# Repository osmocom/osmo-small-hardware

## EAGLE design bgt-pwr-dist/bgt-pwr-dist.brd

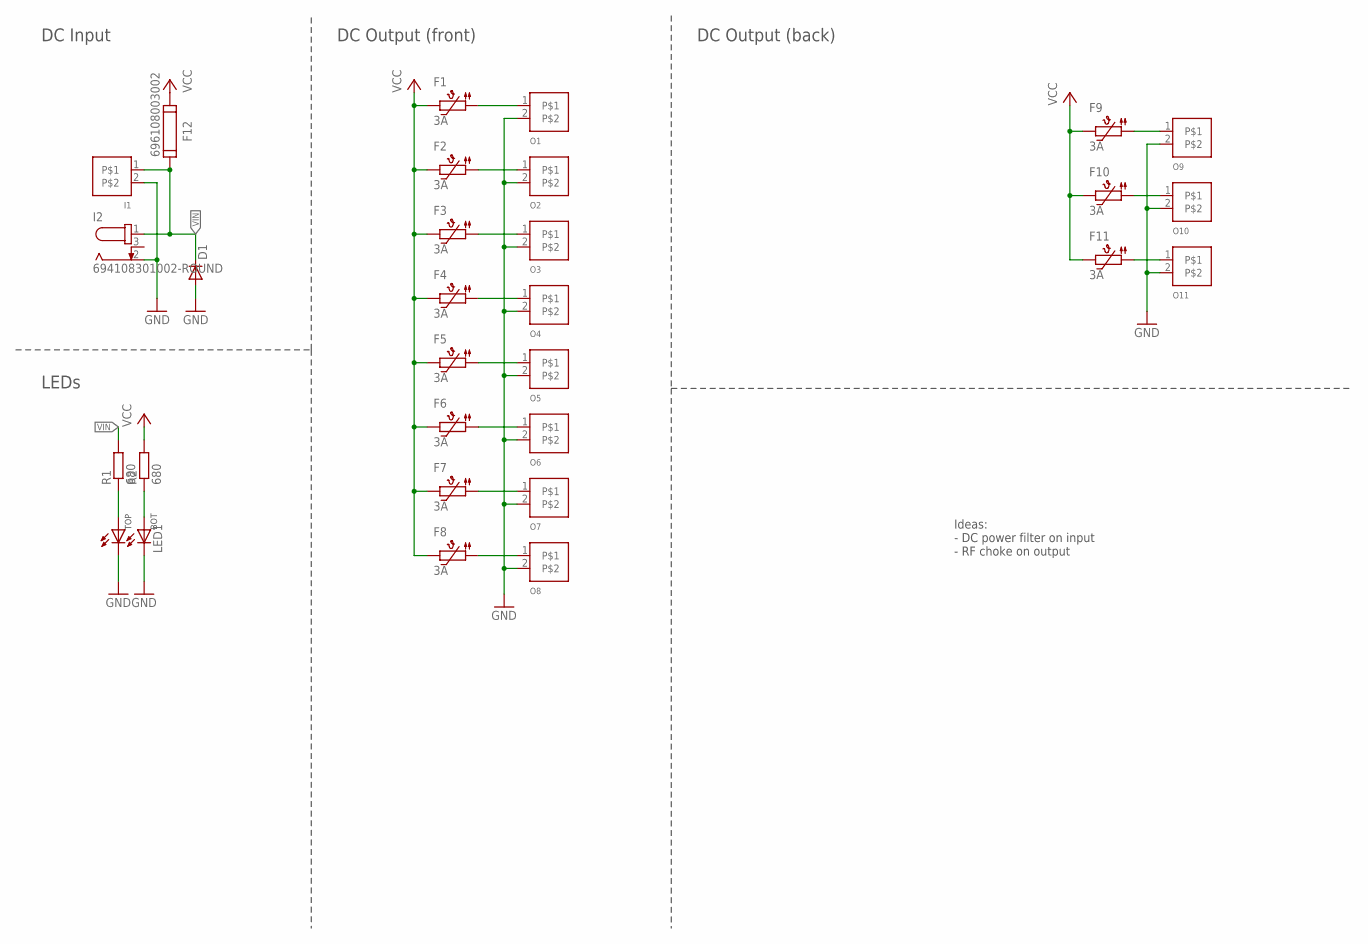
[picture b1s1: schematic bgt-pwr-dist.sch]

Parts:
D1: DIODE-DO201-15; DO201-15; MANUFACTURERPARTNUMBER 1N5351B
F1, F2, F3, F4, F5, F6, F7, F8, F9, F10, F11: 3A; 16R300G; MANUFACTURERPARTNUMBER 16R300GPR
F12: 696108003002; MANUFACTURERPARTNUMBER 696108003002
I1: RIA_1X2-230; RIA230; MANUFACTURERPARTNUMBER TBP01R1-508-02BE
I2: 694108301002-ROUND; 694108301002_ROUND; MANUFACTURERPARTNUMBER 694108301002
LED1: WP934MD; T-1; MANUFACTURERPARTNUMBER WP934MD/2GD
O1, O2, O3, O4, O5, O6, O7, O8, O9, O10, O11: RIA_1X2-382; RIA382-02; MANUFACTURERPARTNUMBER TBP02R1-381-02BE
R1, R2: 680; 0207/10; MANUFACTURERPARTNUMBER CF14JT680R

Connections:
GND: D1.A, I1.2, I2.2, LED1.1 (CT), LED1.3 (CB), O1.2, O2.2, O3.2, O4.2, O5.2, O6.2, O7.2, O8.2, O9.2, O10.2, O11.2
unnamed: F1.1, O1.1
unnamed: F3.1, O3.1
unnamed: F4.1, O4.1
unnamed: F5.1, O5.1
unnamed: F6.1, O6.1
unnamed: F7.1, O7.1
unnamed: F8.1, O8.1
unnamed: LED1.2 (AT), R1.1
unnamed: F9.1, O9.1
unnamed: F10.1, O10.1
unnamed: F11.1, O11.1
unnamed: LED1.4 (AB), R2.1
O2: F2.1, O2.1
VCC: F1.2, F2.2, F3.2, F4.2, F5.2, F6.2, F7.2, F8.2, F9.2, F10.2, F11.2, F12.2, R2.2
VIN: D1.C, F12.1, I1.1, I2.1, R1.2

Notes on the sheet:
Ideas: - DC power filter on input - RF choke on output
DC Input
LEDs
DC Output (front)
DC Output (back)

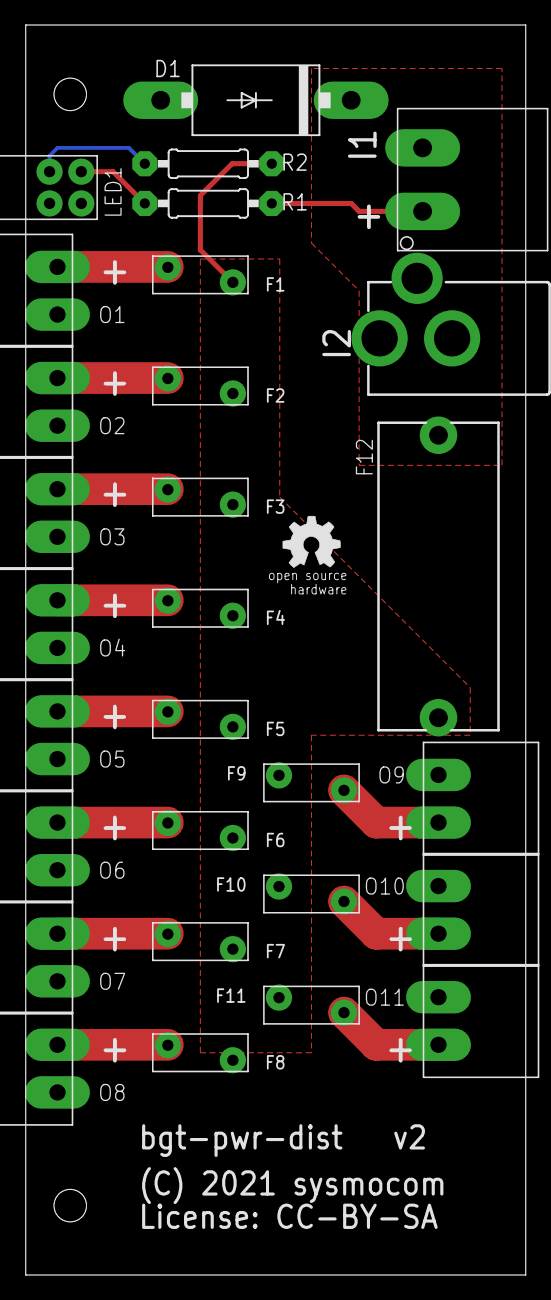
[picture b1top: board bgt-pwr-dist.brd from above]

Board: 2 copper layers, 40.0 x 100.0 mm, 32 parts (1 on the bottom side), 16 nets.

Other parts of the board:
U$1: BGT_3U_160
U$2, U$3: OSHW_5MM

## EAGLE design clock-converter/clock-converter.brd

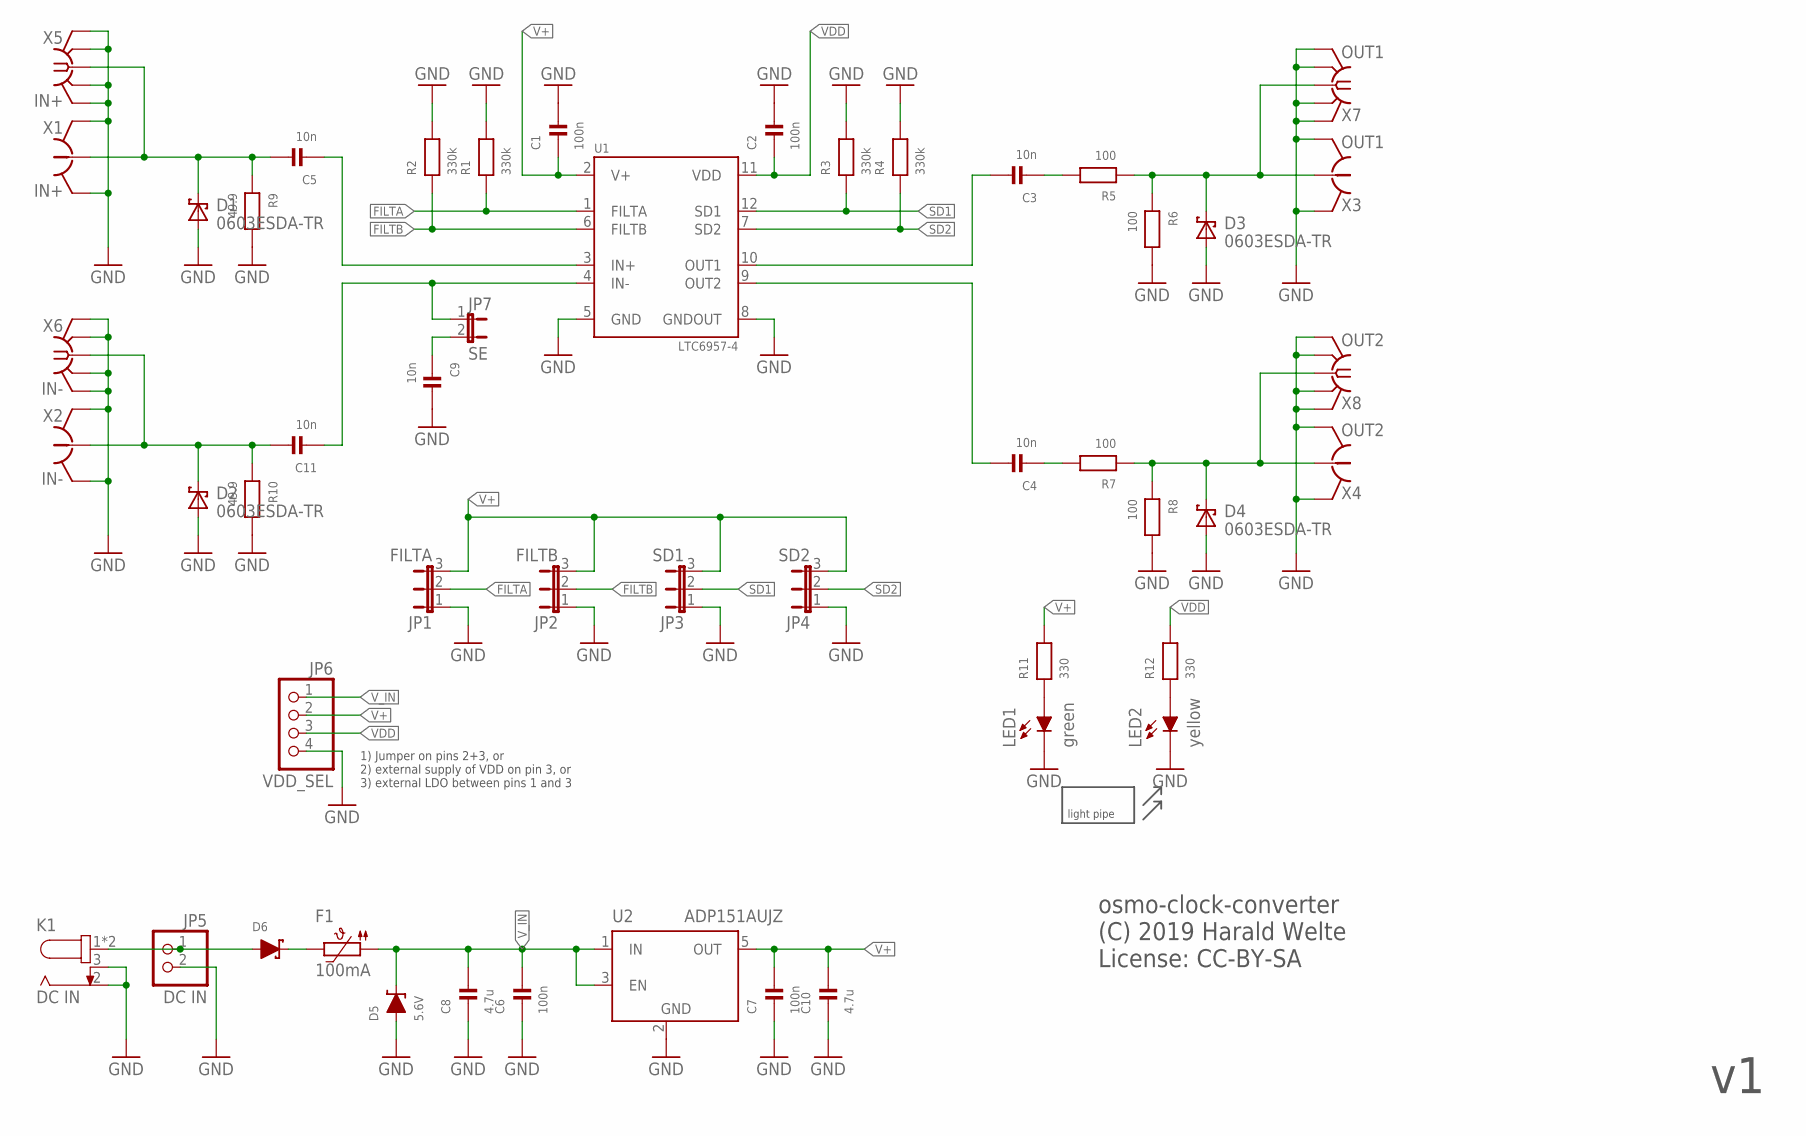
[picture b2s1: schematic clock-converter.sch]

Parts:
C1, C2, C6, C7: 100n; _0603; MANUFACTURERPARTNUMBER CL10B104KO8NNNC
C3, C4, C5, C9, C11: 10n; _0603; MANUFACTURERPARTNUMBER C0603C103M5RACTU
C8, C10: 4.7u; _0805; MANUFACTURERPARTNUMBER CL21A475KOFNNNE
D1, D2, D3, D4: 0603ESDA-TR; 0603; MANUFACTURERPARTNUMBER 0603ESDA2-TR2
D5: 5.6V; SMADIODE; MANUFACTURERPARTNUMBER 3SMAJ5919B-TP
D6: DIODE-SCHOTTKY-SMA; SMADIODE; MANUFACTURERPARTNUMBER CUS08F30,H3F
F1: 100mA; 1206L; MANUFACTURERPARTNUMBER 0ZCJ0020FF2E
JP1: FILTA; JP2; MANUFACTURERPARTNUMBER 61300311121
JP2: FILTB; JP2; MANUFACTURERPARTNUMBER 61300311121
JP3: SD1; JP2; MANUFACTURERPARTNUMBER 61300311121
JP4: SD2; JP2; MANUFACTURERPARTNUMBER 61300311121
JP5: DC IN; 1X02; MANUFACTURERPARTNUMBER PREC002SAAN-RC
JP6: VDD_SEL; 1X04; MANUFACTURERPARTNUMBER PRPC004SAAN-RC
JP7: SE; JP1; MANUFACTURERPARTNUMBER PREC002SAAN-RC
K1: DC IN; 694108106102; MANUFACTURERPARTNUMBER 694108106102
LED1: green; PLCC2-MIN; MANUFACTURERPARTNUMBER LG T67F-R1T1-24
LED2: yellow; PLCC2-MIN; MANUFACTURERPARTNUMBER LY T676-S1T1-26-Z
M1: MENTOR_12701001; 1270.1001; MANUFACTURERPARTNUMBER UNKNOWN MANUFACTURER PART NUMBER
R1, R2, R3, R4: 330k; _0603; MANUFACTURERPARTNUMBER RMCF0603JG330K
R5, R6, R7, R8: 100; _0603; MANUFACTURERPARTNUMBER RMCF0603JT100R
R9, R10: 49.9; _0603; MANUFACTURERPARTNUMBER RMCF0603FT49R9
R11, R12: 330; _0603; MANUFACTURERPARTNUMBER RMCF0603JT330R
U1: LTC6957-4; MSOP12; MANUFACTURERPARTNUMBER LTC6957IMS-3#PBF
U2: ADP151AUJZ; SOT23L; MANUFACTURERPARTNUMBER ADP151AUJZ-3.0-R7
X1: IN+; HRS_UFL; MANUFACTURERPARTNUMBER U.FL-R-SMT(10)
X2: IN-; HRS_UFL; MANUFACTURERPARTNUMBER U.FL-R-SMT(10)
X3: OUT1; HRS_UFL; MANUFACTURERPARTNUMBER U.FL-R-SMT(10)
X4: OUT2; HRS_UFL; MANUFACTURERPARTNUMBER U.FL-R-SMT(10)
X5: IN+; SMA-F-S-TH; MANUFACTURERPARTNUMBER 619540-1
X6: IN-; SMA-F-S-TH; MANUFACTURERPARTNUMBER 619540-1
X7: OUT1; SMA-F-S-TH; MANUFACTURERPARTNUMBER 619540-1
X8: OUT2; SMA-F-S-TH; MANUFACTURERPARTNUMBER 619540-1

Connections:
FILTA: JP1.2, R1.1, U1.1 (FILTA)
FILTB: JP2.2, R2.1, U1.6 (FILTB)
GND: C1.2, C2.2, C6.1, C7.1, C8.1, C9.2, C10.1, D1.1 (A), D2.1 (A), D3.1 (A), D4.1 (A), D5.A, JP1.1, JP2.1, JP3.1, JP4.1, JP5.2, JP6.4, K1.2, K1.3, LED1.K (C), LED2.K (C), R1.2, R2.2, R3.2, R4.2, R6.2, R8.2, R9.2, R10.2, U1.5 (GND), U1.8 (GNDOUT), U2.2 (GND), X1.GND@1 (GND), X1.GND@2 (GND), X2.GND@1 (GND), X2.GND@2 (GND), X3.GND@1 (GND), X3.GND@2 (GND), X4.GND@1 (GND), X4.GND@2 (GND), X5.G1 (GND), X5.G2 (GND), X5.G3 (GND), X5.G4 (GND), X6.G1 (GND), X6.G2 (GND), X6.G3 (GND), X6.G4 (GND), X7.G1 (GND), X7.G2 (GND), X7.G3 (GND), X7.G4 (GND), X8.G1 (GND), X8.G2 (GND), X8.G3 (GND), X8.G4 (GND)
IN+: C5.1, U1.3 (IN+)
unnamed: LED1.A, R11.1
unnamed: C3.2, U1.10 (OUT1)
unnamed: LED2.A, R12.1
unnamed: C9.1, JP7.2
unnamed: D6.C, F1.2
unnamed: C3.1, R5.2
unnamed: C11.1, JP7.1, U1.4 (IN-)
unnamed: C4.2, U1.9 (OUT2)
unnamed: C4.1, R7.2
unnamed: C11.2, D2.2 (K), R10.1, X2.SIG (1), X6.C (1)
unnamed: C5.2, D1.2 (K), R9.1, X1.SIG (1), X5.C (1)
unnamed: D6.A, JP5.1, K1.1, K1.1-1 (1)
OUT1: D3.2 (K), R5.1, R6.1, X3.SIG (1), X7.C (1)
OUT2: D4.2 (K), R7.1, R8.1, X4.SIG (1), X8.C (1)
SD1: JP3.2, R3.1, U1.12 (SD1)
SD2: JP4.2, R4.1, U1.7 (SD2)
V+: C1.1, C7.2, C10.2, JP1.3, JP2.3, JP3.3, JP4.3, JP6.2, R11.2, U1.2 (V+), U2.5 (OUT)
VDD: C2.1, JP6.3, R12.2, U1.11 (VDD)
V_IN: C6.2, C8.2, D5.C, F1.1, JP6.1, U2.1 (IN), U2.3 (EN)

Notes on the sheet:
1) Jumper on pins 2+3, or 2) external supply of VDD on pin 3, or 3) external LDO between pins 1 and 3
osmo-clock-converter (C) 2019 Harald Welte License: CC-BY-SA

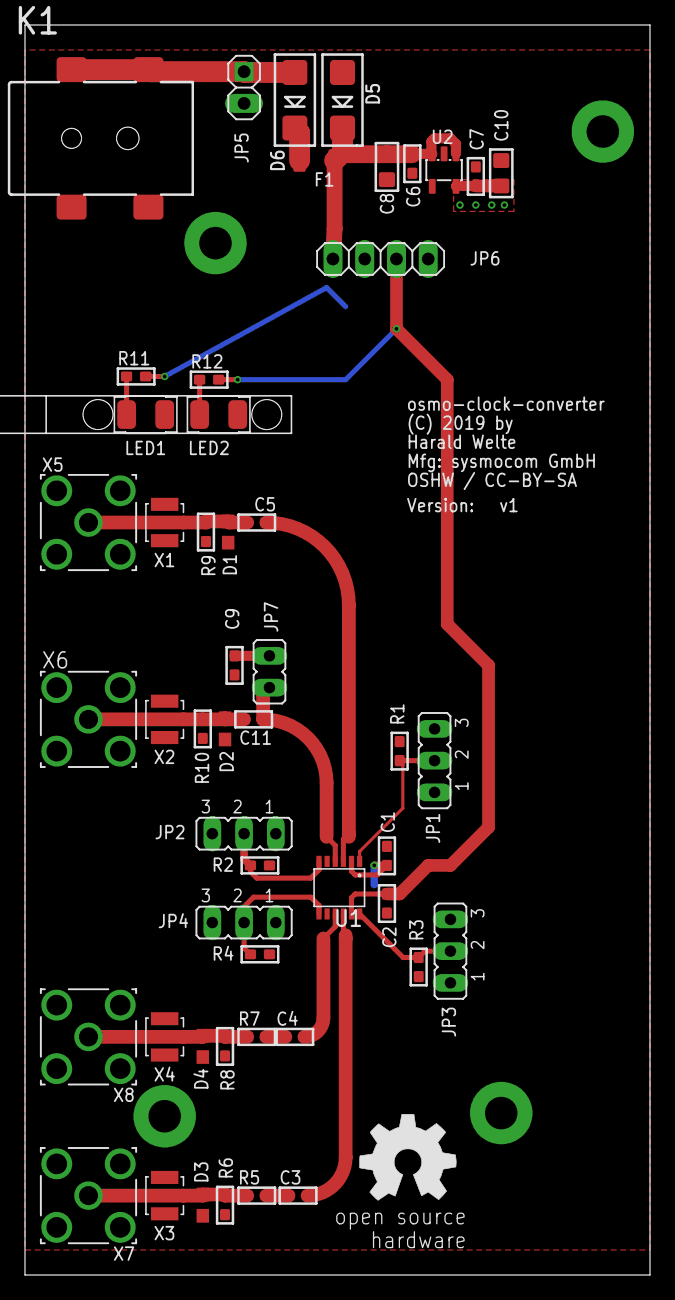
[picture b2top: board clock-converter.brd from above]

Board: 2 copper layers, 50.0 x 100.0 mm, 52 parts (0 on the bottom side), 23 nets.

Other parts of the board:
U$1: OSHW_8MM

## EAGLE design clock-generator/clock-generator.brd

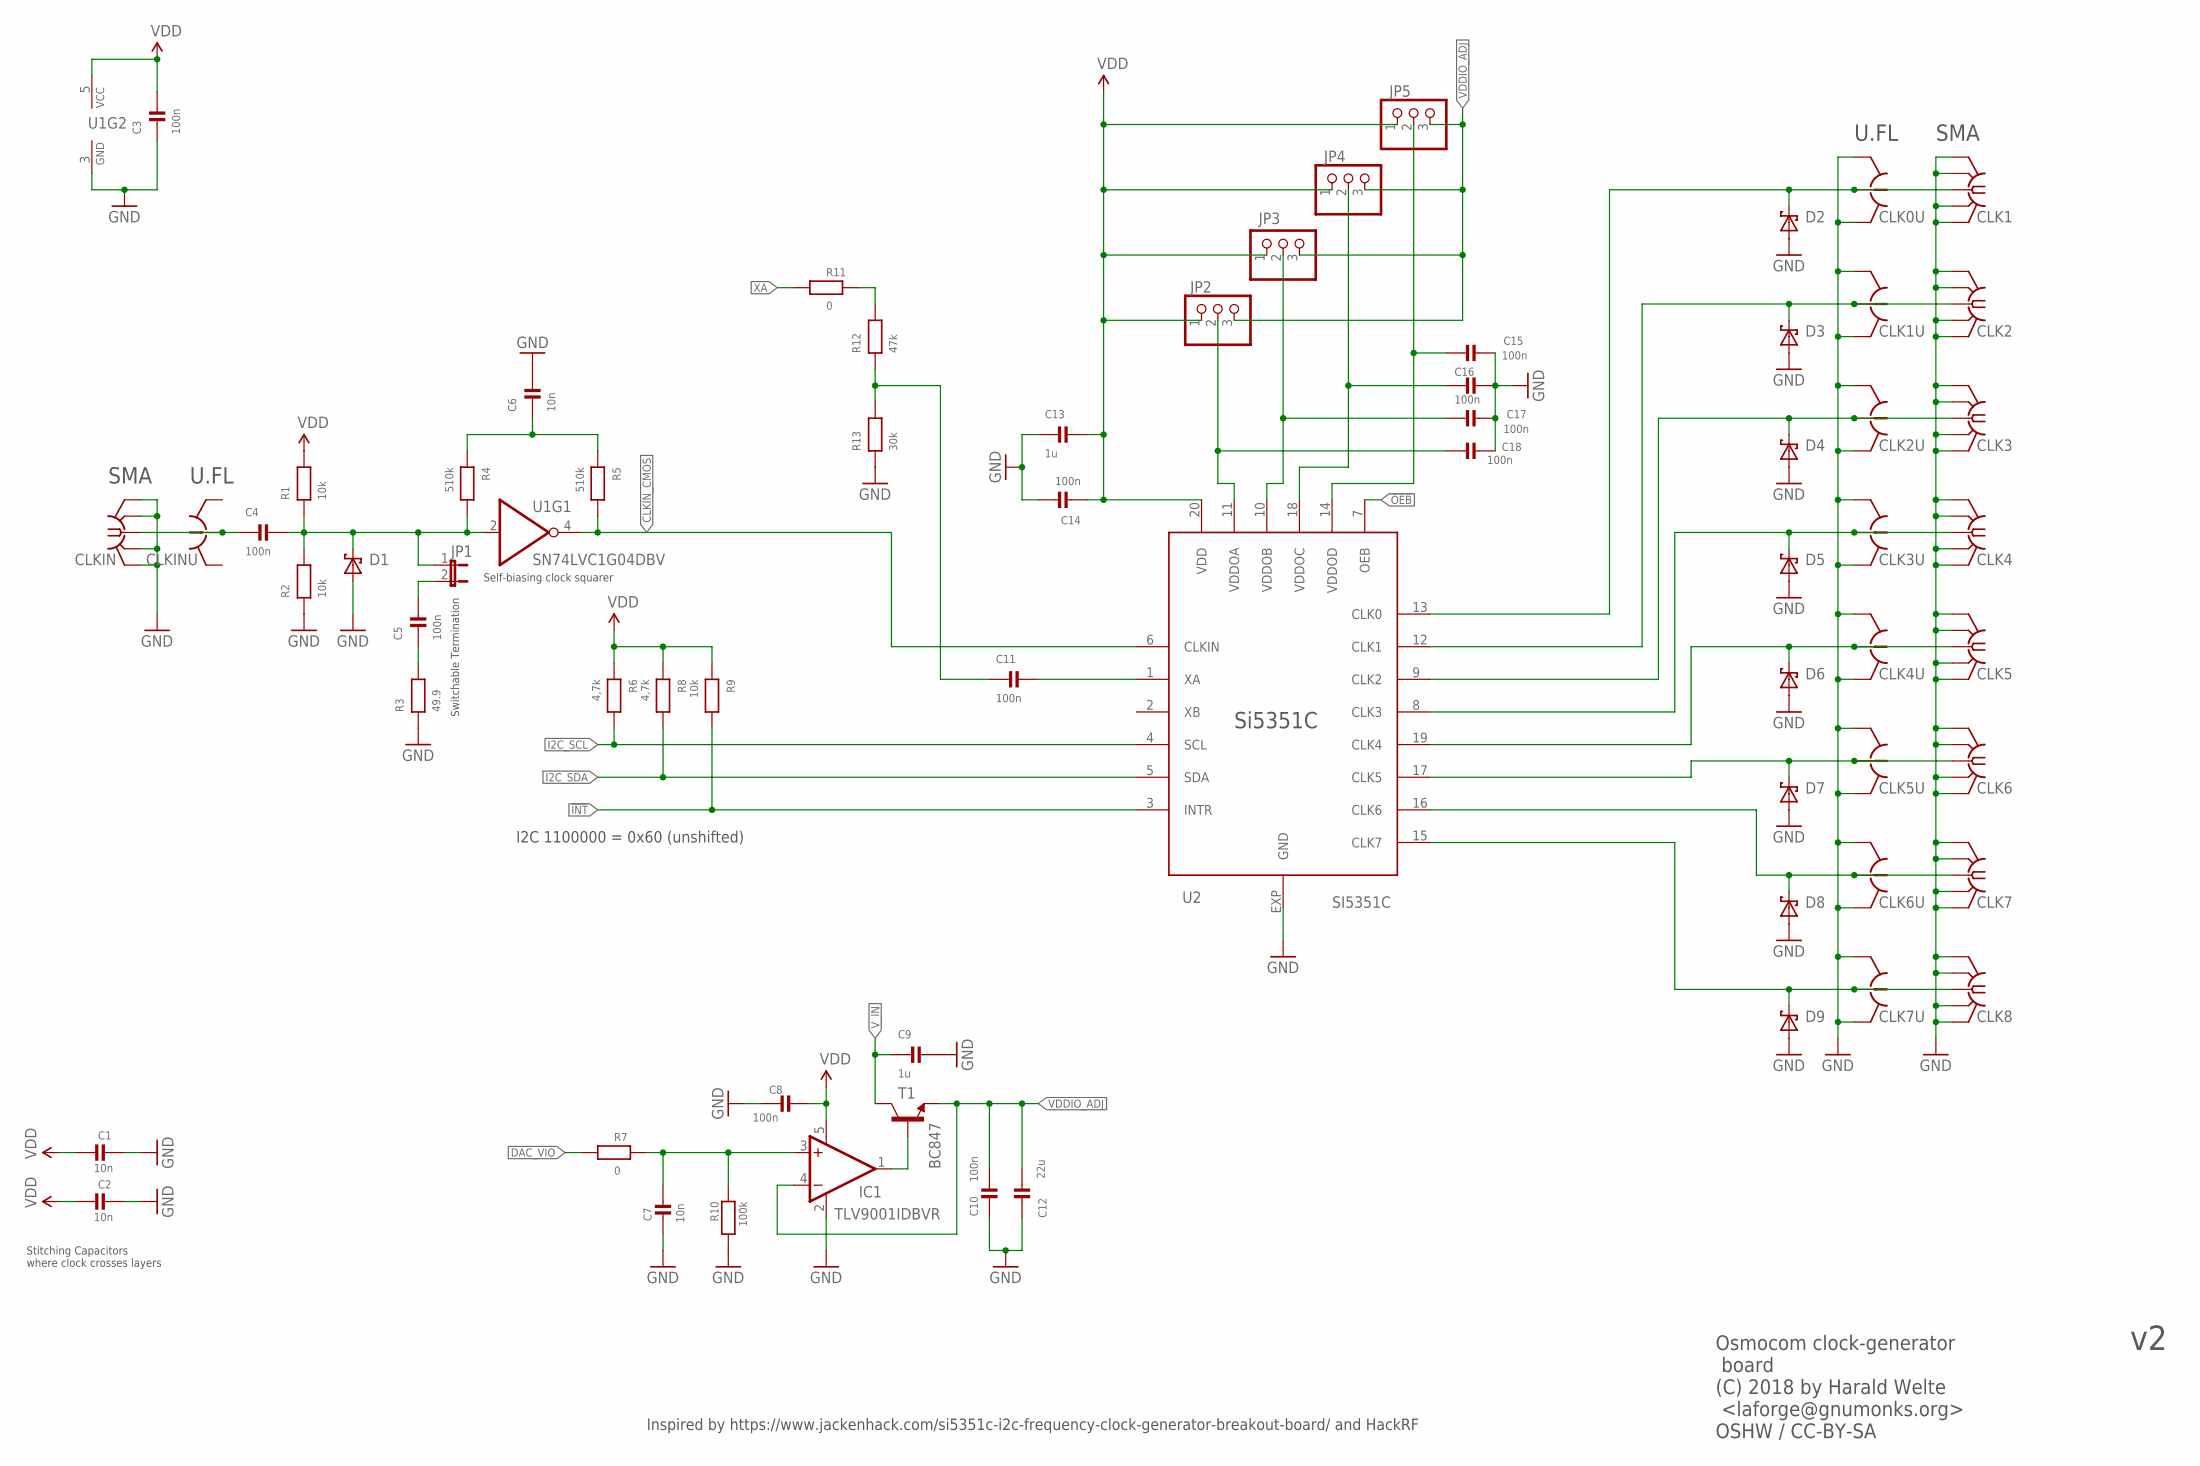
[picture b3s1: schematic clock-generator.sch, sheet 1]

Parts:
C1, C2, C6, C7: 10n; _0402; MANUFACTURERPARTNUMBER CL05B103KA5NNNC
C3, C4, C5, C11, C14: 100n; _0603; MANUFACTURERPARTNUMBER CL10B104KO8NNNC
C8, C10, C15, C16, C17, C18: 100n; _0402; MANUFACTURERPARTNUMBER GCM155R71C104KA55J
C9, C13: 1u; _0603; MANUFACTURERPARTNUMBER CL10A105KP8NNNC
C12: 22u; _0805; MANUFACTURERPARTNUMBER CL21A226MQQNNNE
CLK0U, CLK1U, CLK2U, CLK3U, CLK4U, CLK5U, CLK6U, CLK7U: HRS_UFL; MANUFACTURERPARTNUMBER U.FL-R-SMT(10)
CLK1, CLK2, CLK3, CLK4, CLK5, CLK6, CLK7, CLK8: SMA-F-S-TH; MANUFACTURERPARTNUMBER 619540-1
CLKIN: SMA-F-S-TH; MANUFACTURERPARTNUMBER 619540-1
CLKINU: HRS_UFL; MANUFACTURERPARTNUMBER U.FL-R-SMT(10)
D1, D2, D3, D4, D5, D6, D7, D8, D9: 0603ESDA-TR; 0603; MANUFACTURERPARTNUMBER 0603ESDA2-TR2
IC1: TLV9001IDBVR; SOT23-5; MANUFACTURERPARTNUMBER TLV9001IDBVR
JP1: JP1E; JP1; MANUFACTURERPARTNUMBER PREC002SAAN-RC
JP2, JP3, JP4, JP5: PINHD-1X03_2.54-S; 1X03-S; MANUFACTURERPARTNUMBER UNKNOWN MANUFACTURER PART NUMBER
R1, R2, R9: 10k; _0603; MANUFACTURERPARTNUMBER RMCF0603JT10K0
R3: 49.9; _0603; MANUFACTURERPARTNUMBER RMCF0603FT49R9
R4, R5: 510k; _0603; MANUFACTURERPARTNUMBER RC0603FR-07510KL
R6, R8: 4,7k; _0603; MANUFACTURERPARTNUMBER RC0603JR-074K7L
R7, R11: 0; _0603; MANUFACTURERPARTNUMBER RC1608J000CS
R10: 100k; _0603; MANUFACTURERPARTNUMBER RC0603JR-07100KL
R12: 47k; _0603; MANUFACTURERPARTNUMBER RC0603JR-0747KL
R13: 30k; _0603; MANUFACTURERPARTNUMBER RC0603JR-0730KL
T1: BC847; SOT23-BEC; MANUFACTURERPARTNUMBER BC847C,215
U1: SN74LVC1G04DBV; DBV0005A; MANUFACTURERPARTNUMBER SN74LVC1G04DBVR
U2: SI5351C; QFN-20; MANUFACTURERPARTNUMBER SI5351C-B-GMR

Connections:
!INT: R9.2, U2.3 (INTR); also elsewhere on the board
!OEB: U2.7 (OEB); also elsewhere on the board
CLK0_LINE: CLK0U.SIG (1), CLK1.C (1), D2.2 (K), U2.13 (CLK0)
CLK1_LINE: CLK1U.SIG (1), CLK2.C (1), D3.2 (K), U2.12 (CLK1)
CLK2_LINE: CLK2U.SIG (1), CLK3.C (1), D4.2 (K), U2.9 (CLK2)
CLK3_LINE: CLK3U.SIG (1), CLK4.C (1), D5.2 (K), U2.8 (CLK3)
CLK4_LINE: CLK4U.SIG (1), CLK5.C (1), D6.2 (K), U2.19 (CLK4)
CLK5_LINE: CLK5U.SIG (1), CLK6.C (1), D7.2 (K), U2.17 (CLK5)
CLK6_LINE: CLK6U.SIG (1), CLK7.C (1), D8.2 (K), U2.16 (CLK6)
CLK7_LINE: CLK7U.SIG (1), CLK8.C (1), D9.2 (K), U2.15 (CLK7)
CLKIN: C4.1, CLKIN.C (1), CLKINU.SIG (1)
CLKIN_AC: C4.2, D1.2 (K), JP1.1, R1.1, R2.2, R4.2, U1.2 (I)
CLKIN_CMOS: R5.2, U1.4 (O), U2.6 (CLKIN)
DAC_VIO: R7.2; also elsewhere on the board
GND: C1.1, C2.1, C3.1, C6.2, C7.1, C8.1, C9.2, C10.1, C12.1, C13.1, C14.2, C15.2, C16.2, C17.2, C18.2, CLK0U.GND@1 (GND), CLK0U.GND@2 (GND), CLK1.G1 (GND), CLK1.G2 (GND), CLK1.G3 (GND), CLK1.G4 (GND), CLK1U.GND@1 (GND), CLK1U.GND@2 (GND), CLK2.G1 (GND), CLK2.G2 (GND), CLK2.G3 (GND), CLK2.G4 (GND), CLK2U.GND@1 (GND), CLK2U.GND@2 (GND), CLK3.G1 (GND), CLK3.G2 (GND), CLK3.G3 (GND), CLK3.G4 (GND), CLK3U.GND@1 (GND), CLK3U.GND@2 (GND), CLK4.G1 (GND), CLK4.G2 (GND), CLK4.G3 (GND), CLK4.G4 (GND), CLK4U.GND@1 (GND), CLK4U.GND@2 (GND), CLK5.G1 (GND), CLK5.G2 (GND), CLK5.G3 (GND), CLK5.G4 (GND), CLK5U.GND@1 (GND), CLK5U.GND@2 (GND), CLK6.G1 (GND), CLK6.G2 (GND), CLK6.G3 (GND), CLK6.G4 (GND), CLK6U.GND@1 (GND), CLK6U.GND@2 (GND), CLK7.G1 (GND), CLK7.G2 (GND), CLK7.G3 (GND), CLK7.G4 (GND), CLK7U.GND@1 (GND), CLK7U.GND@2 (GND), CLK8.G1 (GND), CLK8.G2 (GND), CLK8.G3 (GND), CLK8.G4 (GND), CLKIN.G1 (GND), CLKIN.G2 (GND), CLKIN.G3 (GND), CLKIN.G4 (GND), CLKINU.GND@1 (GND), CLKINU.GND@2 (GND), D1.1 (A), D2.1 (A), D3.1 (A), D4.1 (A), D5.1 (A), D6.1 (A), D7.1 (A), D8.1 (A), D9.1 (A), IC1.2 (V-), R2.1, R3.1, R10.1, R13.2, U1.3 (GND), U2.EXP (GND); also elsewhere on the board
I2C_SCL: R6.2, U2.4 (SCL); also elsewhere on the board
I2C_SDA: R8.2, U2.5 (SDA); also elsewhere on the board
unnamed: R11.1, R12.1
unnamed: C5.1, R3.2
unnamed: C11.1, R12.2, R13.1
unnamed: C6.1, R4.1, R5.1
unnamed: C5.2, JP1.2
unnamed: C11.2, U2.1 (XA)
unnamed: C7.2, IC1.3 (+IN), R7.1, R10.2
unnamed: IC1.1 (OUT), T1.B
VDD: C1.2, C2.2, C3.2, C8.2, C13.2, C14.1, IC1.5 (V+), JP2.1, JP3.1, JP4.1, JP5.1, R1.2, R6.1, R8.1, R9.1, U1.5 (VCC), U2.20 (VDD); also elsewhere on the board
VDDIO_ADJ: C10.2, C12.2, IC1.4 (-IN), JP2.3, JP3.3, JP4.3, JP5.3, T1.E
VDDOA: C18.1, JP2.2, U2.11 (VDDOA)
VDDOB: C17.1, JP3.2, U2.10 (VDDOB)
VDDOC: C16.1, JP4.2, U2.18 (VDDOC)
VDDOD: C15.1, JP5.2, U2.14 (VDDOD)
V_IN: C9.1, T1.C; also elsewhere on the board
XA: R11.2; also elsewhere on the board

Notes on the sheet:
Switchable Termination
Self-biasing clock squarer
I2C 1100000 = 0x60 (unshifted)
Stitching Capacitors where clock crosses layers
SMA
U.FL
Si5351C
Osmocom clock-generator board (C) 2018 by Harald Welte <laforge@gnumonks.org> OSHW / CC-BY-SA
Inspired by https://www.jackenhack.com/si5351c-i2c-frequency-clock-generator-breakout-board/ and HackRF

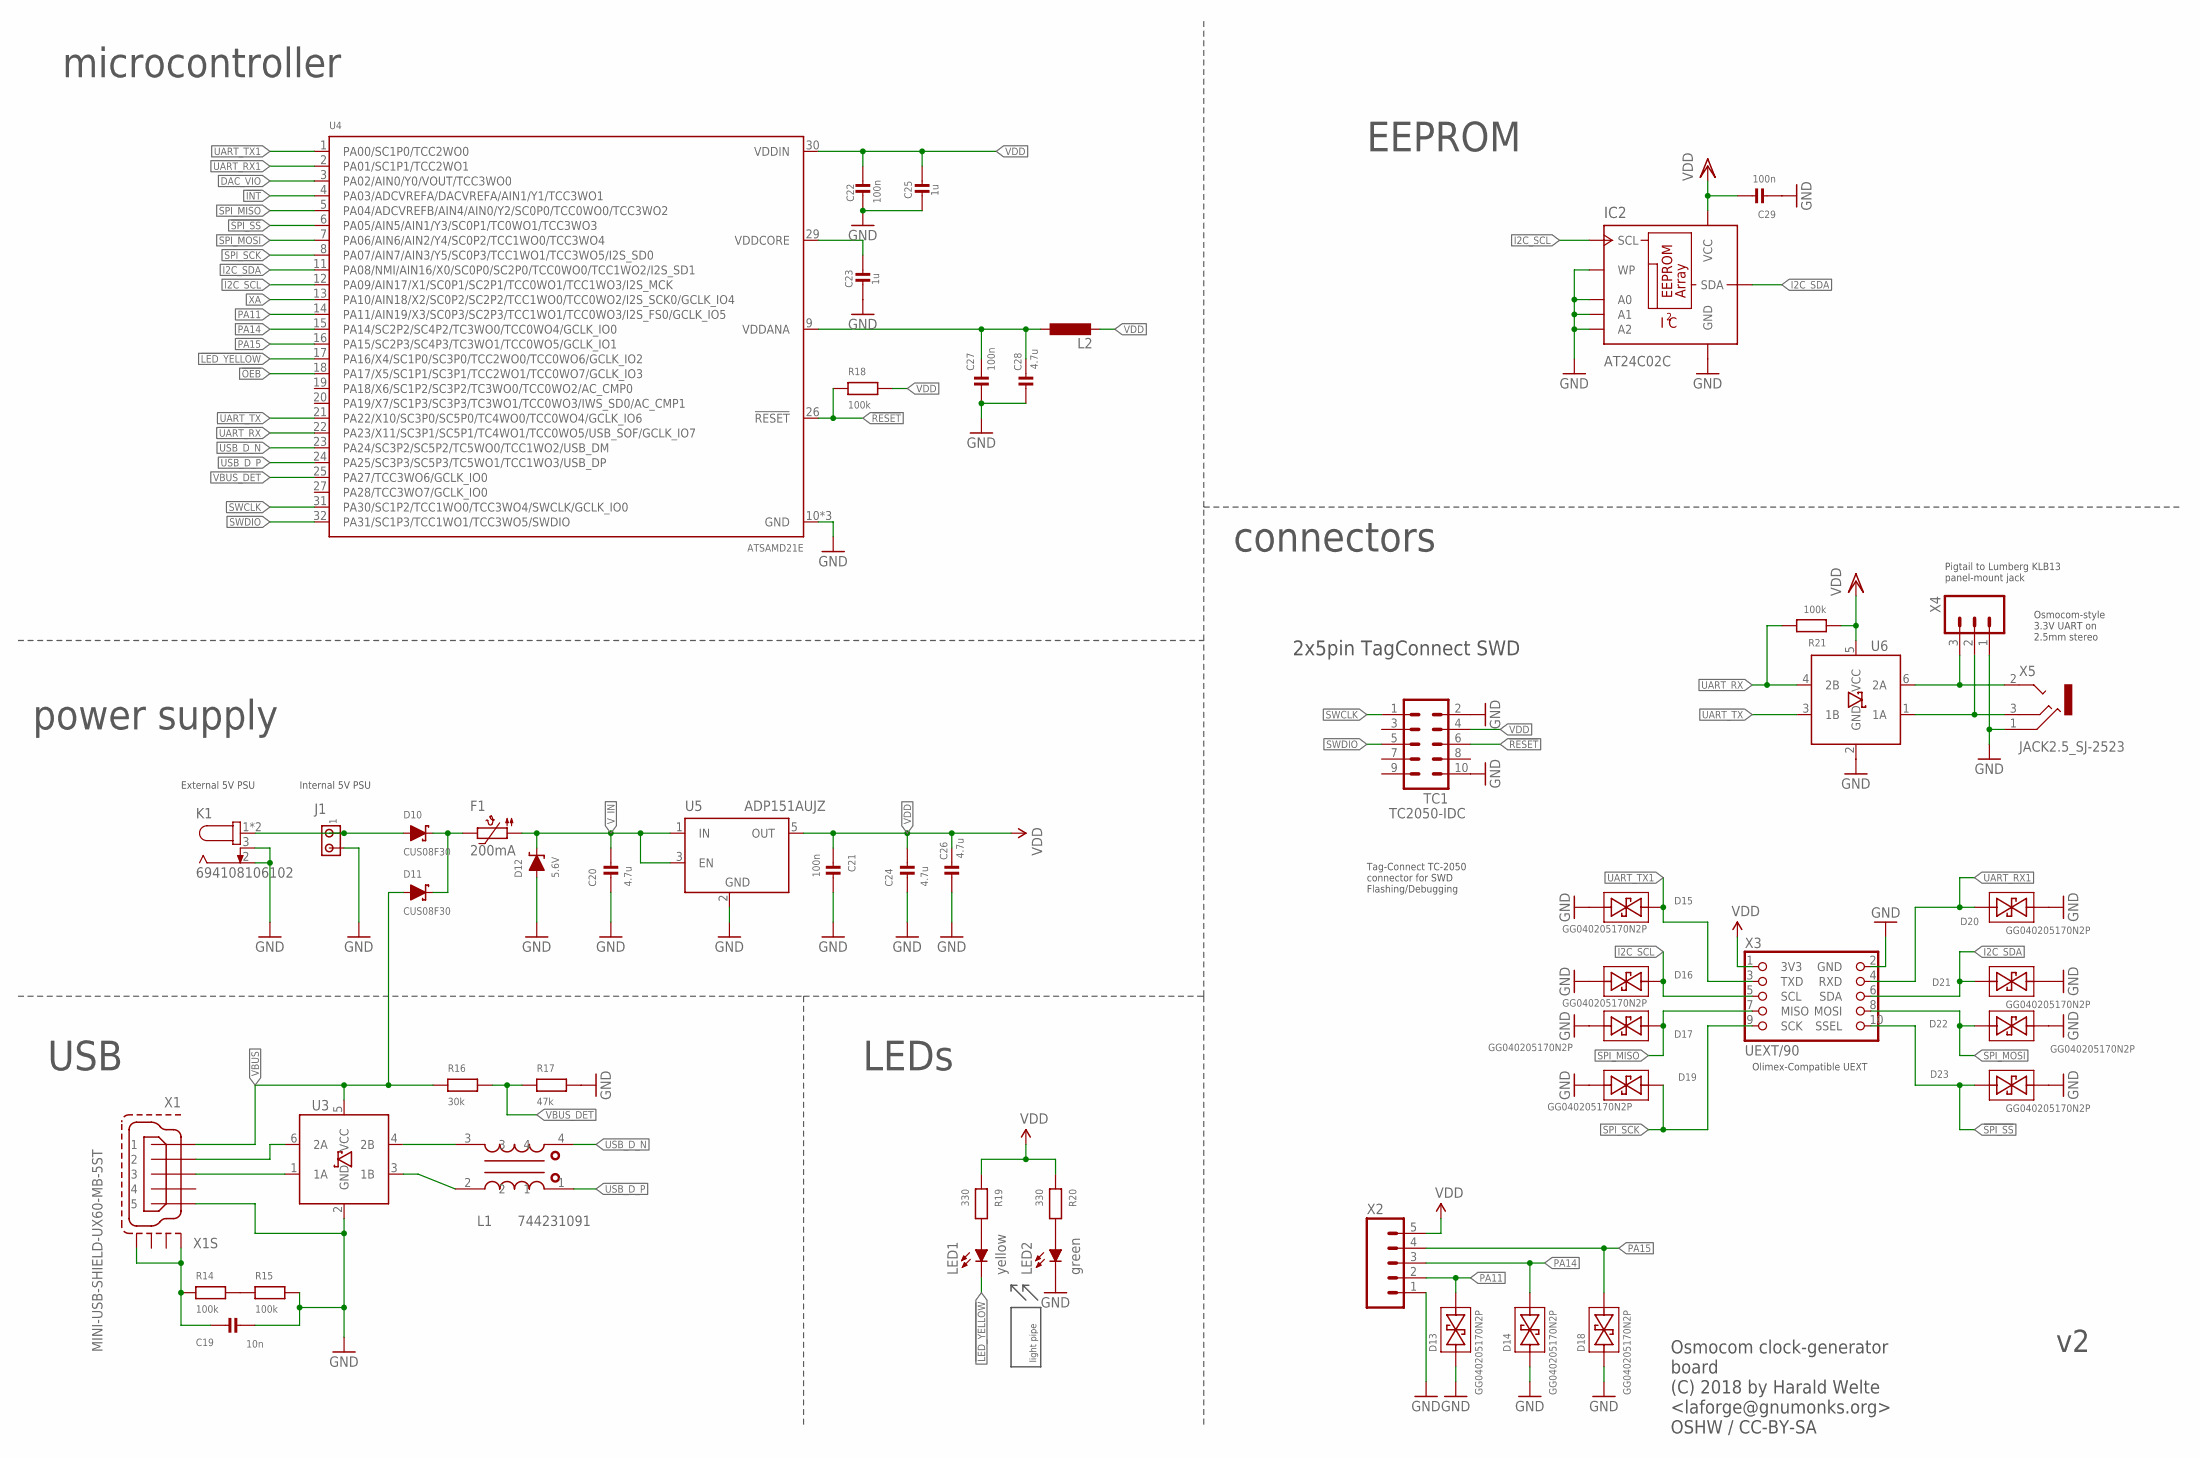
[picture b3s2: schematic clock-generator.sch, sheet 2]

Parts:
C19: 10n; _0402; MANUFACTURERPARTNUMBER CL05B103KA5NNNC
C20, C24, C26, C28: 4.7u; _0805; MANUFACTURERPARTNUMBER CL21A475KOFNNNE
C21, C29: 100n; _0603; MANUFACTURERPARTNUMBER CL10B104KO8NNNC
C22, C27: 100n; _0402; MANUFACTURERPARTNUMBER GCM155R71C104KA55J
C23, C25: 1u; _0603; MANUFACTURERPARTNUMBER CL10A105KP8NNNC
D10, D11: CUS08F30; SOD-323; MANUFACTURERPARTNUMBER CUS08F30,H3F
D12: 5.6V; SMADIODE; MANUFACTURERPARTNUMBER 3SMAJ5919B-TP
D13, D14, D15, D16, D17, D18, D19, D20, D21, D22, D23: GG040205170N2P; _0402; MANUFACTURERPARTNUMBER GG040205170N2P
F1: 200mA; 1206L; MANUFACTURERPARTNUMBER 0ZCJ0020FF2E
IC2: AT24C02C; TSSOP8; MANUFACTURERPARTNUMBER AT24C02C-XHM-T
J1: MTA02-100; 10X02MTA; MANUFACTURERPARTNUMBER UNKNOWN MANUFACTURER PART NUMBER
K1: 694108106102; MANUFACTURERPARTNUMBER 694108106102
L1: 744231091; WE-CNSW_0805; MANUFACTURERPARTNUMBER 744231091
L2: INDUCTOR_0805; _0805; MANUFACTURERPARTNUMBER 742792096
LED1: yellow; PLCC2-MIN; MANUFACTURERPARTNUMBER LY T676-S1T1-26-Z
LED2: green; PLCC2-MIN; MANUFACTURERPARTNUMBER LG T67F-R1T1-24
M1: MENTOR_12701001; 1270.1001; MANUFACTURERPARTNUMBER UNKNOWN MANUFACTURER PART NUMBER
R14, R15, R18, R21: 100k; _0603; MANUFACTURERPARTNUMBER RC0603JR-07100KL
R16: 30k; _0603; MANUFACTURERPARTNUMBER RC0603JR-0730KL
R17: 47k; _0603; MANUFACTURERPARTNUMBER RC0603JR-0747KL
R19, R20: 330; _0603; MANUFACTURERPARTNUMBER RMCF0603JT330R
TC1: TC2050-IDC; MANUFACTURERPARTNUMBER TC-2050
U3, U6: IP4234CZ6; TSOP-6; MANUFACTURERPARTNUMBER IP4234CZ6,125
U4: ATSAMD21E; QFN32_5X5; MANUFACTURERPARTNUMBER ATSAMD21E18A-MUT
U5: ADP151AUJZ; SOT23L; MANUFACTURERPARTNUMBER ADP151AUJZ-3.0-R7
X1: MINI-USB-SHIELD-UX60-MB-5ST; UX60-MB-5ST; MANUFACTURERPARTNUMBER UX60A-MB-5ST
X2: M05LOCK; 1X05_LOCK; MANUFACTURERPARTNUMBER UNKNOWN MANUFACTURER PART NUMBER
X3: UEXT/90; 2X05/90; MANUFACTURERPARTNUMBER 302-S101
X4: PINHD-1X3LOCK_NO_SILK; 1X03_LOCK_NO_SILK; MANUFACTURERPARTNUMBER UNKNOWN MANUFACTURER PART NUMBER
X5: JACK2.5_SJ-2523; MANUFACTURERPARTNUMBER SJ-2523-SMT-TR

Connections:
!INT: U4.4 (PA03/ADCVREFA/DACVREFA/AIN1/Y1/TCC3WO1); also elsewhere on the board
!LED_YELLOW: LED1.K (C), U4.17 (PA16/X4/SC1P0/SC3P0/TCC2WO0/TCC0WO6/GCL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)
!OEB: U4.18 (PA17/X5/SC1P1/SC3P1/TCC2WO1/TCC0WO7/GCL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); also elsewhere on the board
!RESET: R18.2, TC1.6, U4.26 (!RESET)
!SPI_SS: D23.2, U4.6 (PA05/AIN5/AIN1/Y3/SC0P1/TC0WO1/TCC3WO3), X3.10 (SSEL)
DAC_VIO: U4.3 (PA02/AIN0/Y0/VOUT/TCC3WO0); also elsewhere on the board
GND: C19.2, C20.1, C21.2, C22.1, C23.1, C24.1, C25.1, C26.1, C27.1, C28.1, C29.1, D12.A, D13.1, D14.1, D15.2, D16.2, D17.2, D18.1, D19.1, D20.1, D21.1, D22.1, D23.1, IC2.1 (A0), IC2.2 (A1), IC2.3 (A2), IC2.4 (GND), IC2.7 (WP), J1.2, K1.2, K1.3, LED2.K (C), R15.1, R17.1, TC1.2, TC1.10, U3.2 (GND), U4.10 (GND), U4.28 (GND), U4.EXP (GND), U5.2 (GND), U6.2 (GND), X1.5, X2.1, X3.2 (GND), X4.1, X5.1 (RING); also elsewhere on the board
I2C_SCL: D16.1, IC2.6 (SCL), U4.12 (PA09/AIN17/X1/SC0P1/SC2P1/TCC0WO1/TCC1W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), X3.5 (SCL); also elsewhere on the board
I2C_SDA: D21.2, IC2.5 (SDA), U4.11 (PA08/NMI/AIN16/X0/SC0P0/SC2P0/TCC0WO0/T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), X3.6 (SDA); also elsewhere on the board
unnamed: C23.2, U4.29 (VDDCORE)
unnamed: D10.C, D11.C, F1.2
unnamed: LED2.A, R20.1
unnamed: LED1.A, R19.1
unnamed: C27.2, C28.2, L2.1, U4.9 (VDDANA)
unnamed: D10.A, J1.1, K1.1, K1.1-1 (1)
unnamed: R14.1, R15.2
unnamed: C19.1, R14.2, X1.M1 (S1), X1.M4 (S4)
PA11: D13.2, U4.14 (PA11/AIN19/X3/SC0P3/SC2P3/TCC1WO1/TCC0W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), X2.2
PA14: D14.2, U4.15 (PA14/SC2P2/SC4P2/TC3WO0/TCC0WO4/GCLK_IO0), X2.3
PA15: D18.2, U4.16 (PA15/SC2P3/SC4P3/TC3WO1/TCC0WO5/GCLK_IO1), X2.4
SPI_MISO: D17.1, U4.5 (PA04/ADCVREFB/AIN4/AIN0/Y2/SC0P0/TCC0WO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), X3.7 (MISO)
SPI_MOSI: D22.2, U4.7 (PA06/AIN6/AIN2/Y4/SC0P2/TCC1WO0/TCC3WO4), X3.8 (MOSI)
SPI_SCK: D19.2, U4.8 (PA07/AIN7/AIN3/Y5/SC0P3/TCC1WO1/TCC3WO5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), X3.9 (SCK)
SWCLK: TC1.1, U4.31 (PA30/SC1P2/TCC1WO0/TCC3WO4/SWCLK/GCLK_I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)
SWDIO: TC1.5, U4.32 (PA31/SC1P3/TCC1WO1/TCC3WO5/SWDIO)
UART_RX: R21.1, U4.22 (PA23/X11/SC3P1/SC5P1/TC4WO1/TCC0WO5/USB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), U6.4 (2B)
UART_RX0: U6.6 (2A), X4.3, X5.2 (TIP)
UART_RX1: D20.2, U4.2 (PA01/SC1P1/TCC2WO1), X3.4 (RXD)
UART_TX: U4.21 (PA22/X10/SC3P0/SC5P0/TC4WO0/TCC0WO4/GCL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), U6.3 (1B)
UART_TX0: U6.1 (1A), X4.2, X5.3 (MIDDLE)
UART_TX1: D15.1, U4.1 (PA00/SC1P0/TCC2WO0), X3.3 (TXD)
USB0_D_N: U3.6 (2A), X1.2
USB0_D_P: U3.1 (1A), X1.3
USB1_D_N: L1.3, U3.4 (2B)
USB1_D_P: L1.2, U3.3 (1B)
USB_D_N: L1.4, U4.23 (PA24/SC3P2/SC5P2/TC5WO0/TCC1WO2/USB_DM)
USB_D_P: L1.1, U4.24 (PA25/SC3P3/SC5P3/TC5WO1/TCC1WO3/USB_DP)
VBUS: D11.A, R16.2, U3.5 (VCC), X1.1
VBUS_DET: R16.1, R17.2, U4.25 (PA27/TCC3WO6/GCLK_IO0)
VDD: C21.1, C22.2, C24.2, C25.2, C26.2, C29.2, IC2.8 (VCC), L2.2, R18.1, R19.2, R20.2, R21.2, TC1.4, U4.30 (VDDIN), U5.5 (OUT), U6.5 (VCC), X2.5, X3.1 (3V3); also elsewhere on the board
V_IN: C20.2, D12.C, F1.1, U5.1 (IN), U5.3 (EN); also elsewhere on the board
XA: U4.13 (PA10/AIN18/X2/SC0P2/SC2P2/TCC1WO0/TCC0W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); also elsewhere on the board

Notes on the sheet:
Olimex-Compatible UEXT
External 5V PSU
Internal 5V PSU
Pigtail to Lumberg KLB13 panel-mount jack
Osmocom-style 3.3V UART on 2.5mm stereo
Tag-Connect TC-2050 connector for SWD Flashing/Debugging
connectors
LEDs
USB
power supply
microcontroller
EEPROM
Osmocom clock-generator board (C) 2018 by Harald Welte <laforge@gnumonks.org> OSHW / CC-BY-SA
2x5pin TagConnect SWD

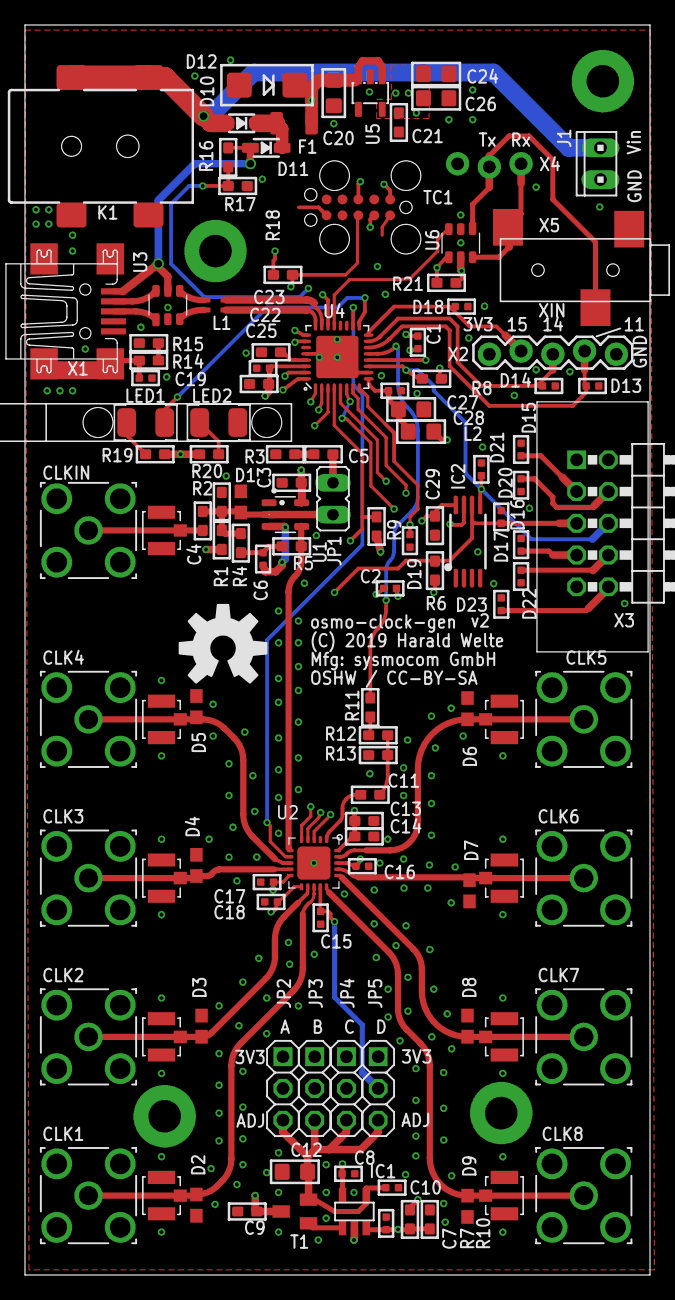
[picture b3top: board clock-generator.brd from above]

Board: 4 copper layers, 50.0 x 100.0 mm, 120 parts (0 on the bottom side), 66 nets.

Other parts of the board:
U$1: OSHW-LOGO-L

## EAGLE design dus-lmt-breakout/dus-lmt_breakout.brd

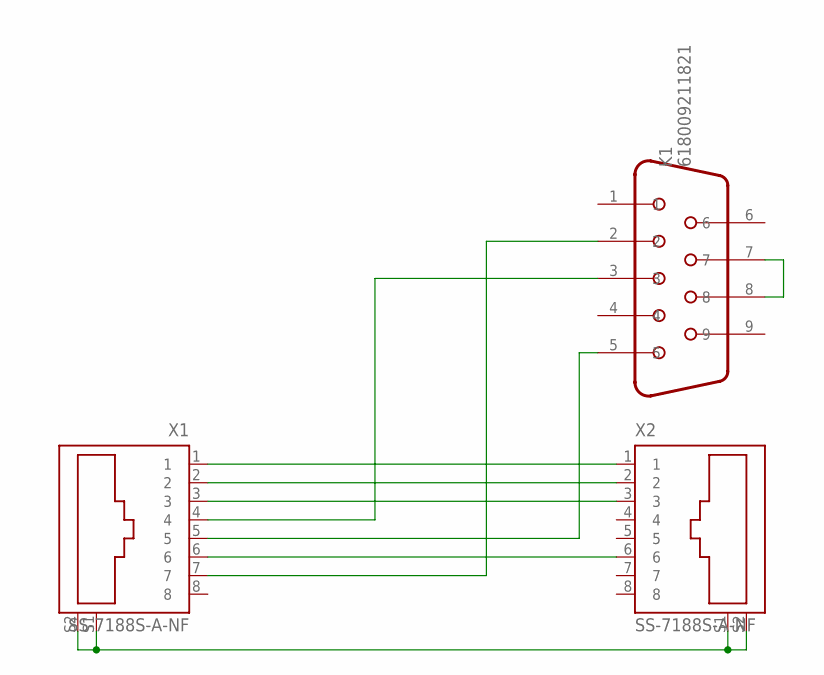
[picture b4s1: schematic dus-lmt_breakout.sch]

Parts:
K1: 618009211821
X1, X2: SS-7188S-A-NF

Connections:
GND: K1.5, X1.5
unnamed: K1.7, K1.8
PAIR12_N: X1.2, X2.2
PAIR12_P: X1.1, X2.1
PAIR36_N: X1.6, X2.6
PAIR36_P: X1.3, X2.3
RS232_COMPUTER_RXD: K1.3, X1.4
RS232_COMPUTER_TXD: K1.2, X1.7
SHIIELD: X1.S1, X1.S2, X2.S1, X2.S2

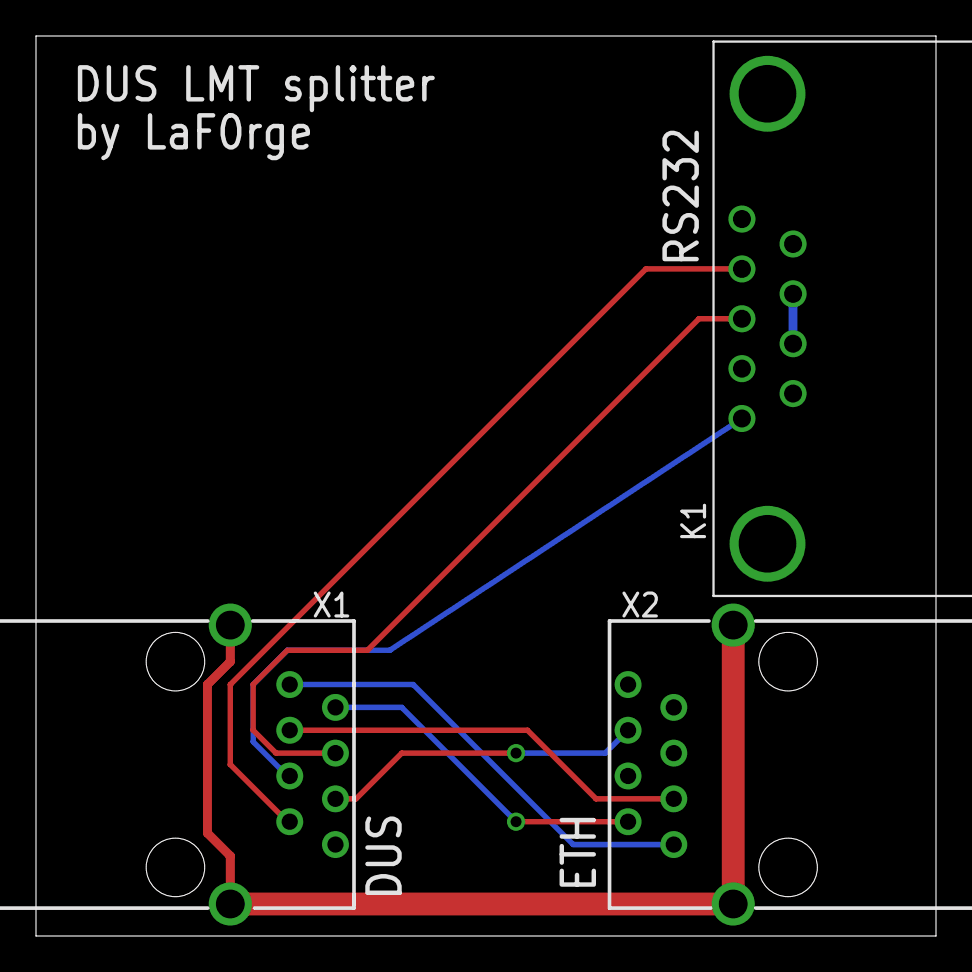
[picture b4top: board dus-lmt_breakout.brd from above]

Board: 2 copper layers, 50.0 x 50.0 mm, 3 parts (0 on the bottom side), 9 nets.

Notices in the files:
bgt-pwr-dist/bgt-pwr-dist.brd:
(C) 2021 sysmocom
License: CC-BY-SA
clock-converter/clock-converter.brd:
(C) 2019 by
Harald Welte
OSHW / CC-BY-SA
mpcie-breakout/mpcie-breakout.brd:
(C) 2016 Harald Welte
parts and their libraries:
Wurth_Elektronik_Electromechanic_DC_Powe: Copyright: Würth Elektronik
atmel-arm: Copyright (C) 2008-2009, Bob Starr
SparkFun-Connectors: Licensing: Creative Commons ShareAlike 4.0 International - https://creativecommons.org/licenses/by-sa/4.0
